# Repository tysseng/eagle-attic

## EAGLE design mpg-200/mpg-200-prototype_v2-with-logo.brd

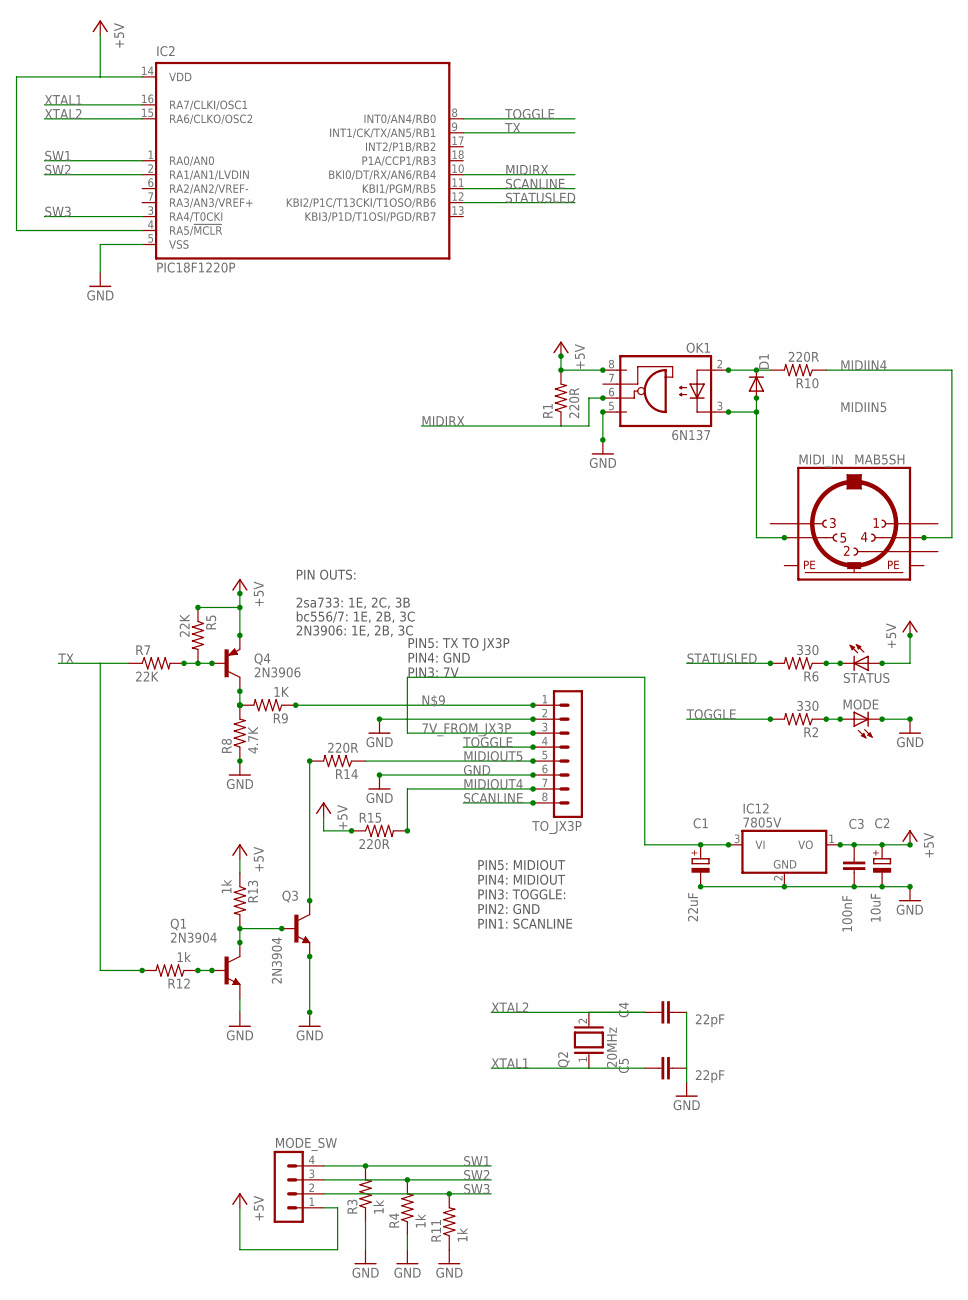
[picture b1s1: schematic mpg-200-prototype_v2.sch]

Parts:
C1: 22uF; E2,5-5
C2: 10uF; E2,5-5
C3: 100nF; C0805
C4, C5: 22pF; C0805
D1: DIODE-SOD80C; SOD80C
IC2: PIC18F1220P; DIL18
IC12: 7805V; TO92
MIDI_IN: MAB5SH
MODE: LED3MM
MODE_SW: MA04-1
OK1: 6N137; DIL08
Q1, Q3: 2N3904; TO92
Q2: 20MHz; QS
Q4: 2N3906; TO92
R1, R10, R14, R15: 220R; R0805
R2, R6: 330; R0805
R3, R4, R11, R12, R13: 1k; R0805
R5, R7: 22K; R0805
R8: 4.7K; R0805
R9: 1K; R0805
STATUS: LED3MM
TO_JX3P: MA08-1

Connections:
7V_FROM_JX3P: C1.+, IC12.3 (VI), TO_JX3P.3
+5V: C2.+, C3.1, IC2.4 (RA5/!MCLR), IC2.14 (VDD), IC12.1 (VO), MODE_SW.1, OK1.8 (VCC), Q4.1 (E), R1.2, R5.1, R13.1, R15.1, STATUS.A
GND: C1.-, C2.-, C3.2, C4.2, C5.2, IC2.5 (VSS), IC12.2 (GND), MODE.K (C), OK1.5 (GND), Q1.1 (E), Q3.1 (E), R3.1, R4.1, R8.1, R11.1, TO_JX3P.2, TO_JX3P.6
MIDIIN4: MIDI_IN.4, R10.1
MIDIIN5: D1.A, MIDI_IN.5, OK1.3 (C)
MIDIOUT4: R15.2, TO_JX3P.7
MIDIOUT5: R14.1, TO_JX3P.5
MIDIRX: IC2.10 (BKI0/DT/RX/AN6/RB4), OK1.6 (VO), R1.1
unnamed: R6.1, STATUS.K (C)
unnamed: Q4.2 (B), R5.2, R7.2
unnamed: MODE.A, R2.1
unnamed: Q1.2 (B), R12.1
unnamed: D1.C, OK1.2 (A), R10.2
unnamed: Q4.3 (C), R8.2, R9.2
unnamed: Q1.3 (C), Q3.2 (B), R13.2
unnamed: Q3.3 (C), R14.2
unnamed: R9.1, TO_JX3P.1
PE: MIDI_IN.PE, MIDI_IN.PE@ (PE)
SCANLINE: IC2.11 (KBI1/PGM/RB5), TO_JX3P.8
STATUSLED: IC2.12 (KBI2/P1C/T13CKI/T1OSO/RB6), R6.2
SW1: IC2.1 (RA0/AN0), MODE_SW.4, R3.2
SW2: IC2.2 (RA1/AN1/LVDIN), MODE_SW.3, R4.2
SW3: IC2.3 (RA4/T0CKI), MODE_SW.2, R11.2
TOGGLE: IC2.8 (INT0/AN4/RB0), R2.2, TO_JX3P.4
TX: IC2.9 (INT1/CK/TX/AN5/RB1), R7.1, R12.2
XTAL1: C5.1, IC2.16 (RA7/CLKI/OSC1), Q2.1
XTAL2: C4.1, IC2.15 (RA6/CLKO/OSC2), Q2.2

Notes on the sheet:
2sa733: 1E, 2C, 3B
bc556/7: 1E, 2B, 3C
2N3906: 1E, 2B, 3C
PIN OUTS:
PIN5: MIDIOUT PIN4: MIDIOUT PIN3: TOGGLE: PIN2: GND PIN1: SCANLINE
PIN5: TX TO JX3P PIN4: GND PIN3: 7V

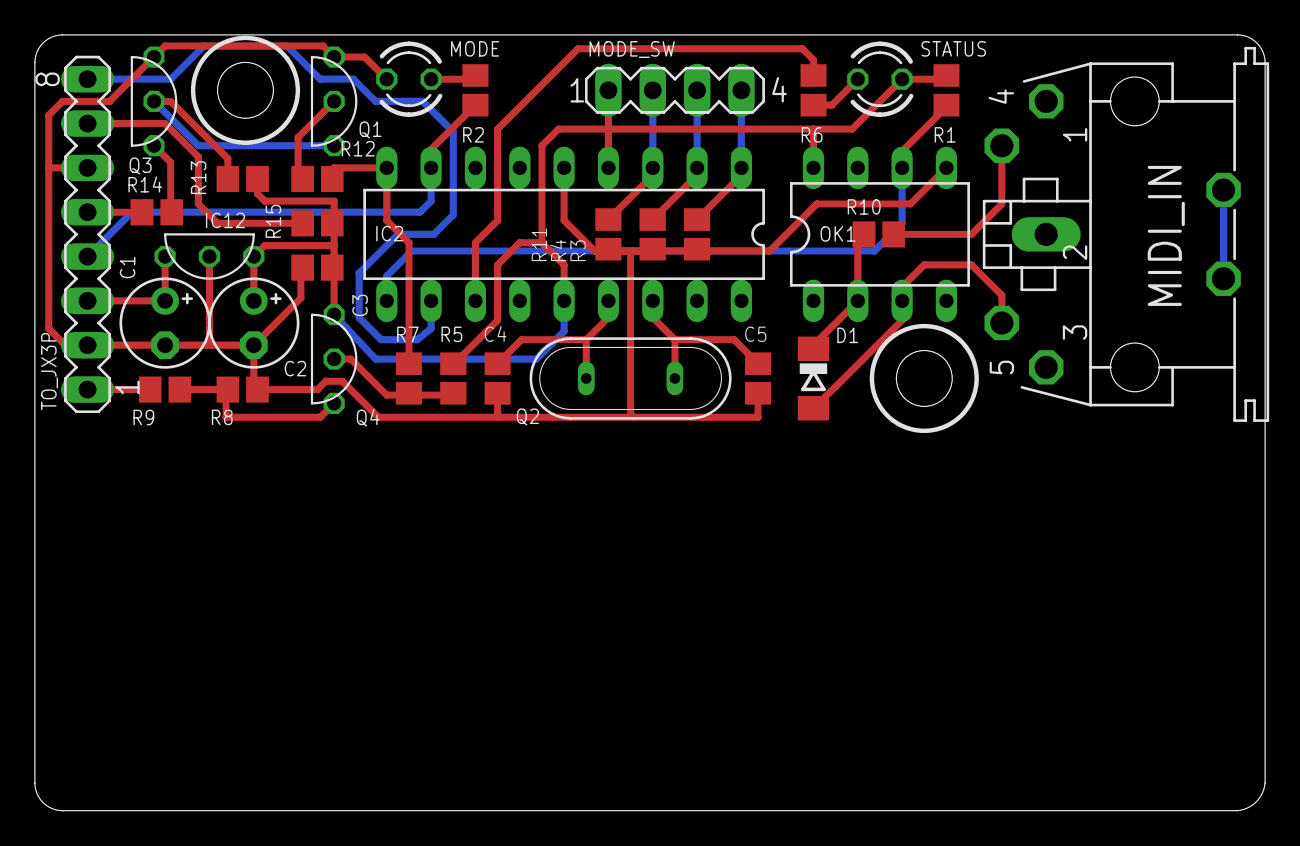
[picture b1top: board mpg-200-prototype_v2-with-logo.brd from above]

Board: 2 copper layers, 70.5 x 44.5 mm, 33 parts (0 on the bottom side), 27 nets.

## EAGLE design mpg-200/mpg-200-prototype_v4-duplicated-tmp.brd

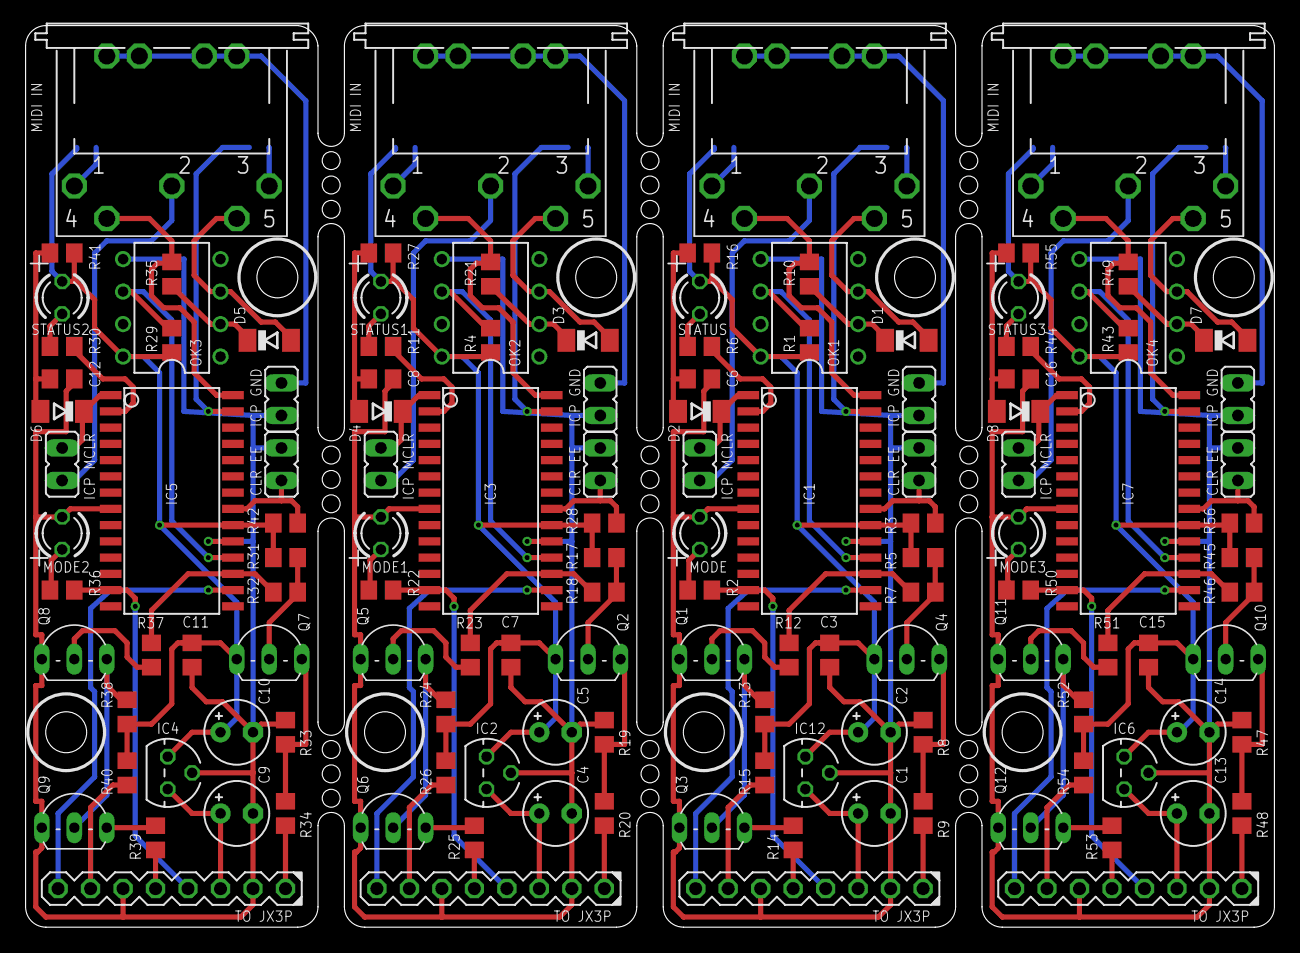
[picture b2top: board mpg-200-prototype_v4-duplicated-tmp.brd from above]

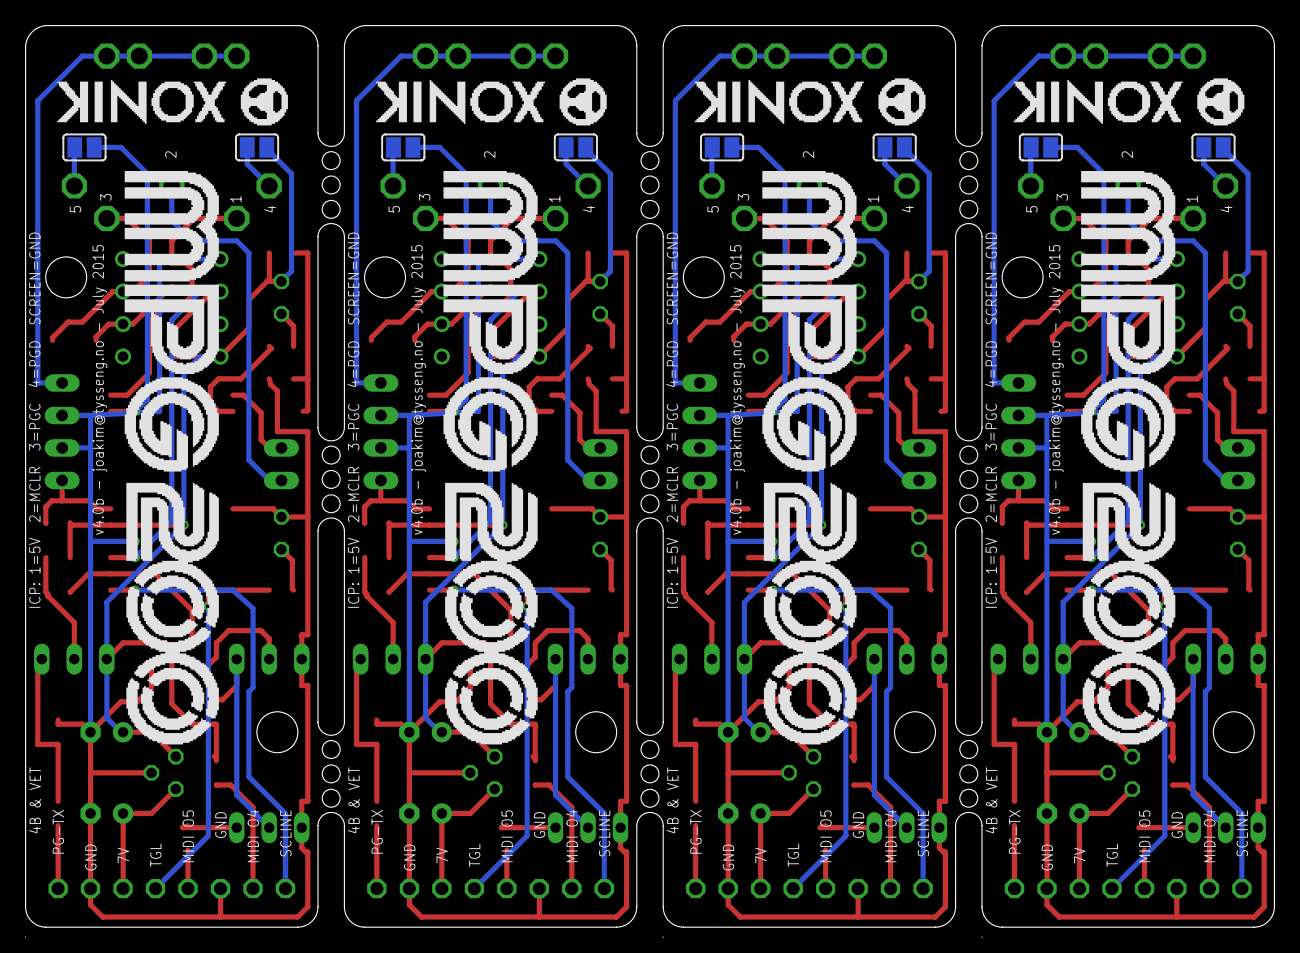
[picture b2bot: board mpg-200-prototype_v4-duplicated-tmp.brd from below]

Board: 2 copper layers, 97.6 x 70.5 mm, 140 parts (8 on the bottom side), 116 nets.

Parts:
C1, C4, C9, C13: 22uF; E2,5-5
C2, C5, C10, C14: 10uF; E2,5-5
C3, C6, C7, C8, C11, C12, C15, C16: 100nF; C0805
D1, D2, D3, D4, D5, D6, D7, D8: SOD80C
IC1, IC3, IC5, IC7: PIC18F2580-E/SO; SO28W
IC2, IC4, IC6, IC12: 7805V; TO92
JP1, JP2, JP3, JP4, JP5, JP6, JP7, JP8, JP9, JP10, JP11, JP12: JP1
MIDI_IN, MIDI_IN1, MIDI_IN2, MIDI_IN3: DIN5-180-J2G-S; DIN5-180-J-DUAL-GND-SHORT
MODE, MODE1, MODE2, MODE3: LED3MM
OK1, OK2, OK3, OK4: 6N137J; DIL08-J
Q1, Q2, Q3, Q4, Q5, Q6, Q7, Q8, Q9, Q10, Q11, Q12: TO92-EBC
R1, R4, R10, R14, R15, R21, R25, R26, R29, R35, R39, R40, R43, R49, R53, R54: 220R; R0805
R2, R6, R11, R22, R30, R36, R44, R50: 330; R0805
R3, R16, R27, R28, R41, R42, R55, R56: 10k; R0805
R5, R7, R17, R18, R31, R32, R45, R46: 22K; R0805
R8, R19, R33, R47: 4.7K; R0805
R9, R20, R34, R48: 1K; R0805
R12, R13, R23, R24, R37, R38, R51, R52: 1k; R0805
SJ1, SJ2, SJ3, SJ4, SJ5, SJ6, SJ7, SJ8: SJ
STATUS, STATUS1, STATUS2, STATUS3: LED3MM
TO_JX3P, TO_JX3P1, TO_JX3P2, TO_JX3P3: MA08-1

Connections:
7V_FROM_JX3P: C1.+, IC12.3, TO_JX3P.3
7V_FROM_JX3P1: C4.+, IC2.3, TO_JX3P1.3
7V_FROM_JX3P2: C9.+, IC4.3, TO_JX3P2.3
7V_FROM_JX3P3: C13.+, IC6.3, TO_JX3P3.3
+5V: C2.+, C3.1, IC1.20, IC12.1, OK1.8, Q4.E, R1.2, R3.2, R5.1, R13.1, R15.1, R16.2, SJ2.2, STATUS.A
+5V1: C5.+, C7.1, IC2.1, IC3.20, OK2.8, Q2.E, R4.2, R17.1, R24.1, R26.1, R27.2, R28.2, SJ4.2, STATUS1.A
+5V2: C10.+, C11.1, IC4.1, IC5.20, OK3.8, Q7.E, R29.2, R31.1, R38.1, R40.1, R41.2, R42.2, SJ6.2, STATUS2.A
+5V3: C14.+, C15.1, IC6.1, IC7.20, OK4.8, Q10.E, R43.2, R45.1, R52.1, R54.1, R55.2, R56.2, SJ8.2, STATUS3.A
CLEAREE: IC1.21, JP3.2, R3.1
CLEAREE1: IC3.21, JP6.2, R28.1
CLEAREE2: IC5.21, JP9.2, R42.1
CLEAREE3: IC7.21, JP12.2, R56.1
GND: C1.-, C2.-, C3.2, C6.2, IC1.8, IC1.19, IC12.2, JP1.2, JP3.1, MODE.K, OK1.5, Q1.E, Q3.E, R8.1, TO_JX3P.2, TO_JX3P.6
GND1: C4.-, C5.-, C7.2, C8.2, IC2.2, IC3.8, IC3.19, JP4.2, JP6.1, MODE1.K, OK2.5, Q5.E, Q6.E, R19.1, TO_JX3P1.2, TO_JX3P1.6
GND2: C9.-, C10.-, C11.2, C12.2, IC4.2, IC5.8, IC5.19, JP7.2, JP9.1, MODE2.K, OK3.5, Q8.E, Q9.E, R33.1, TO_JX3P2.2, TO_JX3P2.6
GND3: C13.-, C14.-, C15.2, C16.2, IC6.2, IC7.8, IC7.19, JP10.2, JP12.1, MODE3.K, OK4.5, Q11.E, Q12.E, R47.1, TO_JX3P3.2, TO_JX3P3.6
MCLR: D2.C, IC1.1, JP2.1
MCLR1: D4.C, IC3.1, JP5.1
MCLR2: D6.C, IC5.1, JP8.1
MCLR3: D8.C, IC7.1, JP11.1
MIDIIN1: IC3.28, MIDI_IN1.4, R21.1
MIDIIN2: D3.A, MIDI_IN1.5, OK2.3
MIDIIN3: IC5.28, MIDI_IN2.4, R35.1
MIDIIN4: IC1.28, MIDI_IN.4, R10.1
MIDIIN5: D1.A, MIDI_IN.5, OK1.3
MIDIIN6: D5.A, MIDI_IN2.5, OK3.3
MIDIIN7: IC7.28, MIDI_IN3.4, R49.1
MIDIIN8: D7.A, MIDI_IN3.5, OK4.3
MIDIOUT1: R25.1, TO_JX3P1.5
MIDIOUT2: R26.2, TO_JX3P1.7
MIDIOUT3: R39.1, TO_JX3P2.5
MIDIOUT4: R15.2, TO_JX3P.7
MIDIOUT5: R14.1, TO_JX3P.5
MIDIOUT6: R40.2, TO_JX3P2.7
MIDIOUT7: R53.1, TO_JX3P3.5
MIDIOUT8: R54.2, TO_JX3P3.7
MIDIRX: IC1.18, OK1.6, R1.1
MIDIRX1: IC3.18, OK2.6, R4.1
MIDIRX2: IC5.18, OK3.6, R29.1
MIDIRX3: IC7.18, OK4.6, R43.1
unnamed: R6.1, STATUS.K
unnamed: Q4.B, R5.2, R7.2
unnamed: MODE.A, R2.1
unnamed: Q1.B, R12.1
unnamed: D1.C, OK1.2, R10.2
unnamed: Q4.C, R8.2, R9.2
unnamed: Q1.C, Q3.B, R13.2
unnamed: Q3.C, R14.2
unnamed: R9.1, TO_JX3P.1
unnamed: MIDI_IN.3, SJ1.2
unnamed: JP2.2, MIDI_IN.2
unnamed: MIDI_IN.1, SJ2.1
unnamed: JP1.1, MIDI_IN.PE, MIDI_IN.PE@1, MIDI_IN.PE@2, MIDI_IN.PE@3
unnamed: C6.1, D2.A, R16.1
unnamed: D3.C, OK2.2, R21.2
unnamed: Q2.B, R17.2, R18.2
unnamed: Q2.C, R19.2, R20.2
unnamed: R11.1, STATUS1.K
unnamed: MODE1.A, R22.1
unnamed: Q5.B, R23.1
unnamed: Q5.C, Q6.B, R24.2
unnamed: Q6.C, R25.2
unnamed: R20.1, TO_JX3P1.1
unnamed: JP4.1, MIDI_IN1.PE, MIDI_IN1.PE@1, MIDI_IN1.PE@2, MIDI_IN1.PE@3
unnamed: MIDI_IN1.3, SJ3.2
unnamed: JP5.2, MIDI_IN1.2
unnamed: MIDI_IN1.1, SJ4.1
unnamed: C8.1, D4.A, R27.1
unnamed: D5.C, OK3.2, R35.2
unnamed: Q7.B, R31.2, R32.2
unnamed: Q7.C, R33.2, R34.2
unnamed: R30.1, STATUS2.K
unnamed: MODE2.A, R36.1
unnamed: Q8.B, R37.1
unnamed: Q8.C, Q9.B, R38.2
unnamed: Q9.C, R39.2
unnamed: R34.1, TO_JX3P2.1
unnamed: JP7.1, MIDI_IN2.PE, MIDI_IN2.PE@1, MIDI_IN2.PE@2, MIDI_IN2.PE@3
unnamed: MIDI_IN2.3, SJ5.2
unnamed: JP8.2, MIDI_IN2.2
unnamed: MIDI_IN2.1, SJ6.1
unnamed: C12.1, D6.A, R41.1
unnamed: D7.C, OK4.2, R49.2
unnamed: Q10.B, R45.2, R46.2
unnamed: Q10.C, R47.2, R48.2
unnamed: R44.1, STATUS3.K
unnamed: MODE3.A, R50.1
unnamed: Q11.B, R51.1
unnamed: Q11.C, Q12.B, R52.2
unnamed: Q12.C, R53.2
unnamed: R48.1, TO_JX3P3.1
unnamed: JP10.1, MIDI_IN3.PE, MIDI_IN3.PE@1, MIDI_IN3.PE@2, MIDI_IN3.PE@3
unnamed: MIDI_IN3.3, SJ7.2
unnamed: JP11.2, MIDI_IN3.2
unnamed: MIDI_IN3.1, SJ8.1
unnamed: C16.1, D8.A, R55.1
PGCLOCK: IC1.27, SJ1.1
PGCLOCK1: IC3.27, SJ3.1
PGCLOCK2: IC5.27, SJ5.1
PGCLOCK3: IC7.27, SJ7.1
SCANLINE: IC1.16, TO_JX3P.8
SCANLINE1: IC3.16, TO_JX3P1.8
SCANLINE2: IC5.16, TO_JX3P2.8
SCANLINE3: IC7.16, TO_JX3P3.8
STATUSLED: IC1.2, R6.2
STATUSLED1: IC3.2, R11.2
STATUSLED2: IC5.2, R30.2
STATUSLED3: IC7.2, R44.2
TOGGLE: IC1.13, R2.2, TO_JX3P.4
TOGGLE1: IC3.13, R22.2, TO_JX3P1.4
TOGGLE2: IC5.13, R36.2, TO_JX3P2.4
TOGGLE3: IC7.13, R50.2, TO_JX3P3.4
TX: IC1.17, R7.1, R12.2
TX1: IC3.17, R18.1, R23.2
TX2: IC5.17, R32.1, R37.2
TX3: IC7.17, R46.1, R51.2
